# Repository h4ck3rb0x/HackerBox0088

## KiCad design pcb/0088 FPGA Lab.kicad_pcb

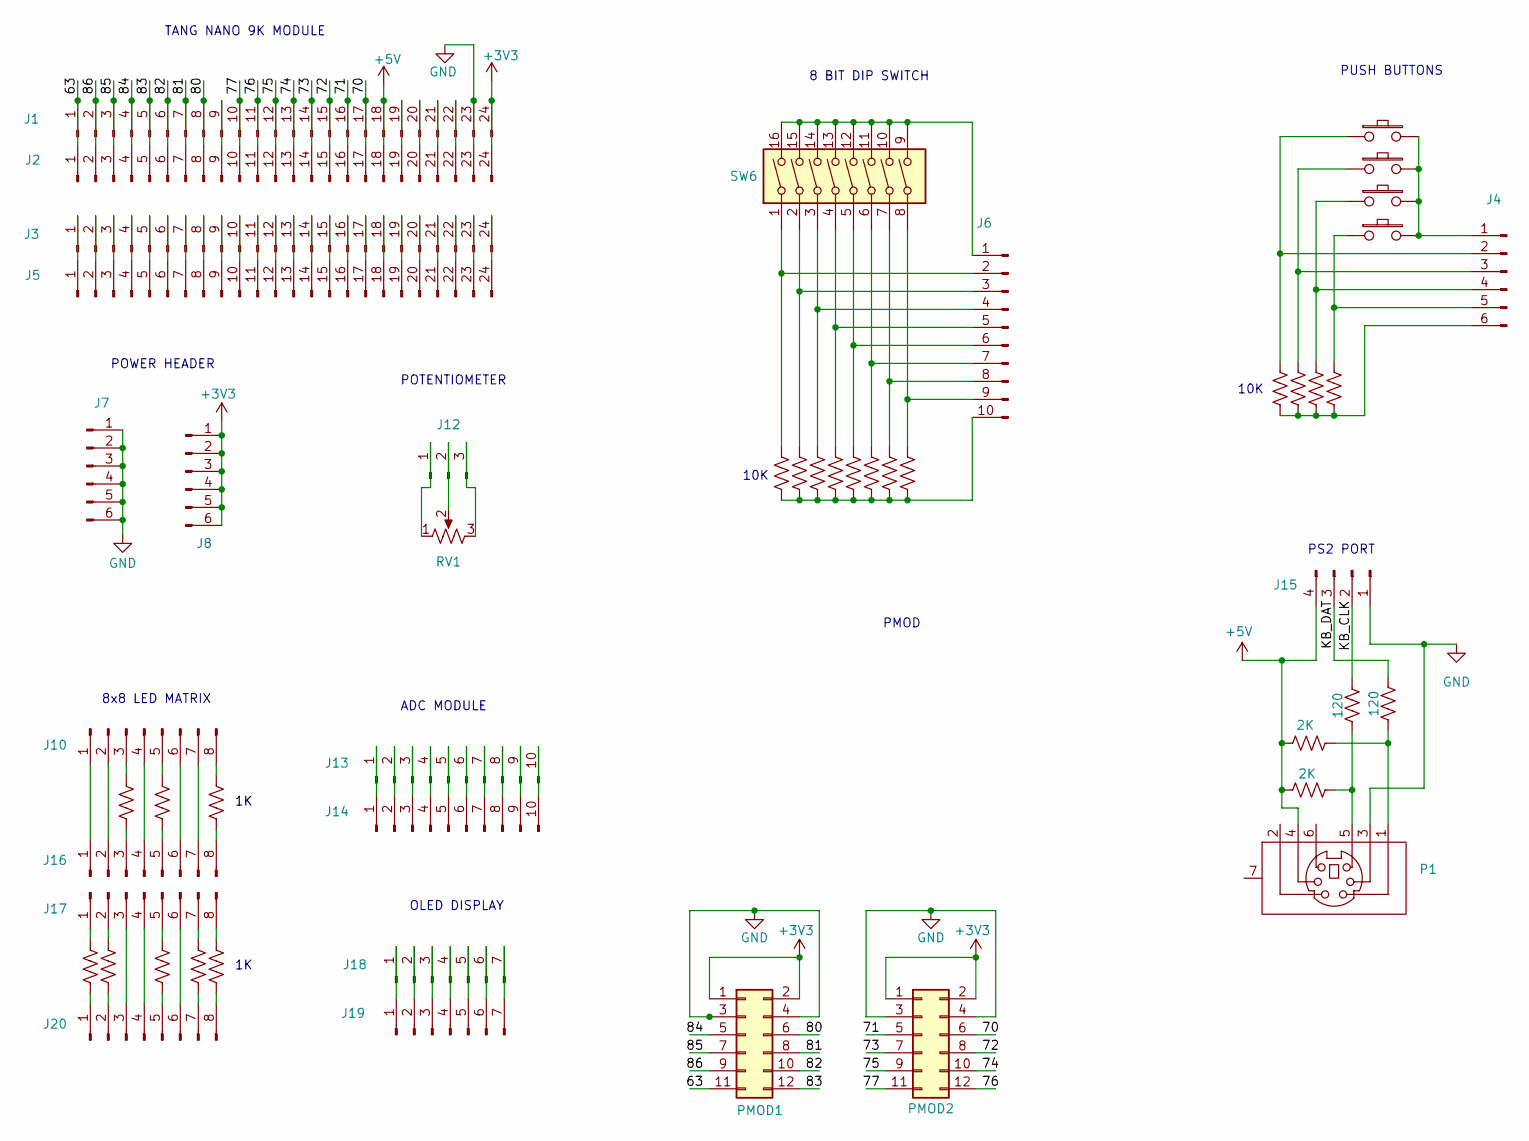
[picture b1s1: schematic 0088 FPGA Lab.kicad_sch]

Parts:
J1, J2, J3, J5: Conn_01x24_Male; PinHeader_1x24_P2.54mm_Vertical
J4, J7, J8: Conn_01x06_Male; PinHeader_1x06_P2.54mm_Vertical
J6, J13, J14: Conn_01x10_Male; PinHeader_1x10_P2.54mm_Vertical
J10, J16, J17, J20: Conn_01x08_Male; PinHeader_1x08_P2.54mm_Vertical
J12: Conn_01x03_Male; PinHeader_1x03_P2.54mm_Vertical
J15: Conn_01x04_Male; PinHeader_1x04_P2.54mm_Vertical
J18, J19: Conn_01x07_Male; PinHeader_1x07_P2.54mm_Vertical
P1: Connector_Mini-DIN_Female_6Pin_2rows
PMOD1, PMOD2: Conn_02x06_Odd_Even; PinSocket_2x06_P2.54mm_Horizontal
R1, R2, R4, R5, R6, R7, R8, R9, R10, R11, R12: 10K; R_1206_3216Metric_Pad1.30x1.75mm_HandSolder
R3: 10k; R_1206_3216Metric_Pad1.30x1.75mm_HandSolder
R13, R14: 2K; R_1206_3216Metric_Pad1.30x1.75mm_HandSolder
R15, R16: 120; R_1206_3216Metric_Pad1.30x1.75mm_HandSolder
R17, R18, R19, R20, R21, R22, R23, R24: 1K; R_1206_3216Metric_Pad1.30x1.75mm_HandSolder
RV1: R_Potentiometer_US; Potentiometer_Bourns_PTV09A-1_Single_Vertical
SW1, SW2, SW3, SW4: SW_PUSH_BUTTON; SW_TH_Tactile_Omron_B3F-10xx
SW6: SW_DIP_x08; SW_DIP_SPSTx08_Slide_9.78x22.5mm_W7.62mm_P2.54mm

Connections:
+5V: J1.18, J2.18, J15.4, P1.4, R13.2, R14.2
/63: J1.1, J2.1, PMOD1.11
/70: J1.17, J2.17, PMOD2.6
/71: J1.16, J2.16, PMOD2.5
/72: J1.15, J2.15, PMOD2.8
/73: J1.14, J2.14, PMOD2.7
/74: J1.13, J2.13, PMOD2.10
/75: J1.12, J2.12, PMOD2.9
/76: J1.11, J2.11, PMOD2.12
/77: J1.10, J2.10, PMOD2.11
/80: J1.8, J2.8, PMOD1.6
/81: J1.7, J2.7, PMOD1.8
/82: J1.6, J2.6, PMOD1.10
/83: J1.5, J2.5, PMOD1.12
/84: J1.4, J2.4, PMOD1.5
/85: J1.3, J2.3, PMOD1.7
/86: J1.2, J2.2, PMOD1.9
/KB_CLK: J15.2, R15.1
/KB_DAT: J15.3, R16.1
unnamed: J1.9, J2.9
unnamed: J1.19, J2.19
unnamed: J1.20, J2.20
unnamed: J1.21, J2.21
unnamed: J1.22, J2.22
unnamed: J3.1, J5.1
unnamed: J3.2, J5.2
unnamed: J3.3, J5.3
unnamed: J3.4, J5.4
unnamed: J3.5, J5.5
unnamed: J3.6, J5.6
unnamed: J3.7, J5.7
unnamed: J3.8, J5.8
unnamed: J3.9, J5.9
unnamed: J3.10, J5.10
unnamed: J3.11, J5.11
unnamed: J3.12, J5.12
unnamed: J3.13, J5.13
unnamed: J3.14, J5.14
unnamed: J3.15, J5.15
unnamed: J3.16, J5.16
unnamed: J3.17, J5.17
unnamed: J3.18, J5.18
unnamed: J3.19, J5.19
unnamed: J3.20, J5.20
unnamed: J3.21, J5.21
unnamed: J3.22, J5.22
unnamed: J3.23, J5.23
unnamed: J3.24, J5.24
unnamed: J4.1, SW1.2, SW2.2, SW3.2, SW4.2
unnamed: J4.2, R1.2, SW1.1
unnamed: J4.3, R2.2, SW2.1
unnamed: J4.4, R3.2, SW3.1
unnamed: J4.5, R4.2, SW4.1
unnamed: J4.6, R1.1, R2.1, R3.1, R4.1
unnamed: J6.1, SW6.9, SW6.10, SW6.11, SW6.12, SW6.13, SW6.14, SW6.15, SW6.16
unnamed: J6.2, R5.2, SW6.1
unnamed: J6.3, R6.2, SW6.2
unnamed: J6.4, R7.2, SW6.3
unnamed: J6.5, R8.2, SW6.4
unnamed: J6.6, R9.2, SW6.5
unnamed: J6.7, R10.2, SW6.6
unnamed: J6.8, R11.2, SW6.7
unnamed: J6.9, R12.2, SW6.8
unnamed: J6.10, R5.1, R6.1, R7.1, R8.1, R9.1, R10.1, R11.1, R12.1
unnamed: J10.1, J16.1
unnamed: J10.2, J16.2
unnamed: J10.3, R17.2
unnamed: J10.4, J16.4
unnamed: J10.5, R18.2
unnamed: J10.6, J16.6
unnamed: J10.7, J16.7
unnamed: J10.8, R19.2
unnamed: J12.1, RV1.1
unnamed: J12.2, RV1.2
unnamed: J12.3, RV1.3
unnamed: J13.1, J14.1
unnamed: J13.2, J14.2
unnamed: J13.3, J14.3
unnamed: J13.4, J14.4
unnamed: J13.5, J14.5
unnamed: J13.6, J14.6
unnamed: J13.7, J14.7
unnamed: J13.8, J14.8
unnamed: J13.9, J14.9
unnamed: J13.10, J14.10
unnamed: J16.3, R17.1
unnamed: J16.5, R18.1
unnamed: J16.8, R19.1
unnamed: J17.1, R20.2
unnamed: J17.2, R21.2
unnamed: J17.3, J20.3
unnamed: J17.4, J20.4
unnamed: J17.5, R22.2
unnamed: J17.6, J20.6
unnamed: J17.7, R23.2
unnamed: J17.8, R24.2
unnamed: J18.1, J19.1
unnamed: J18.2, J19.2
unnamed: J18.3, J19.3
unnamed: J18.4, J19.4
unnamed: J18.5, J19.5
unnamed: J18.6, J19.6
unnamed: J18.7, J19.7
unnamed: J20.1, R20.1
unnamed: J20.2, R21.1
unnamed: J20.5, R22.1
unnamed: J20.7, R23.1
unnamed: J20.8, R24.1
unnamed: P1.1, R13.1, R16.2
unnamed: P1.5, R14.1, R15.2

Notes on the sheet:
10K
8x8 LED MATRIX
ADC MODULE
TANG NANO 9K MODULE
PUSH BUTTONS
8 BIT DIP SWITCH
PS2 PORT
PMOD
POTENTIOMETER
POWER HEADER
OLED DISPLAY

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
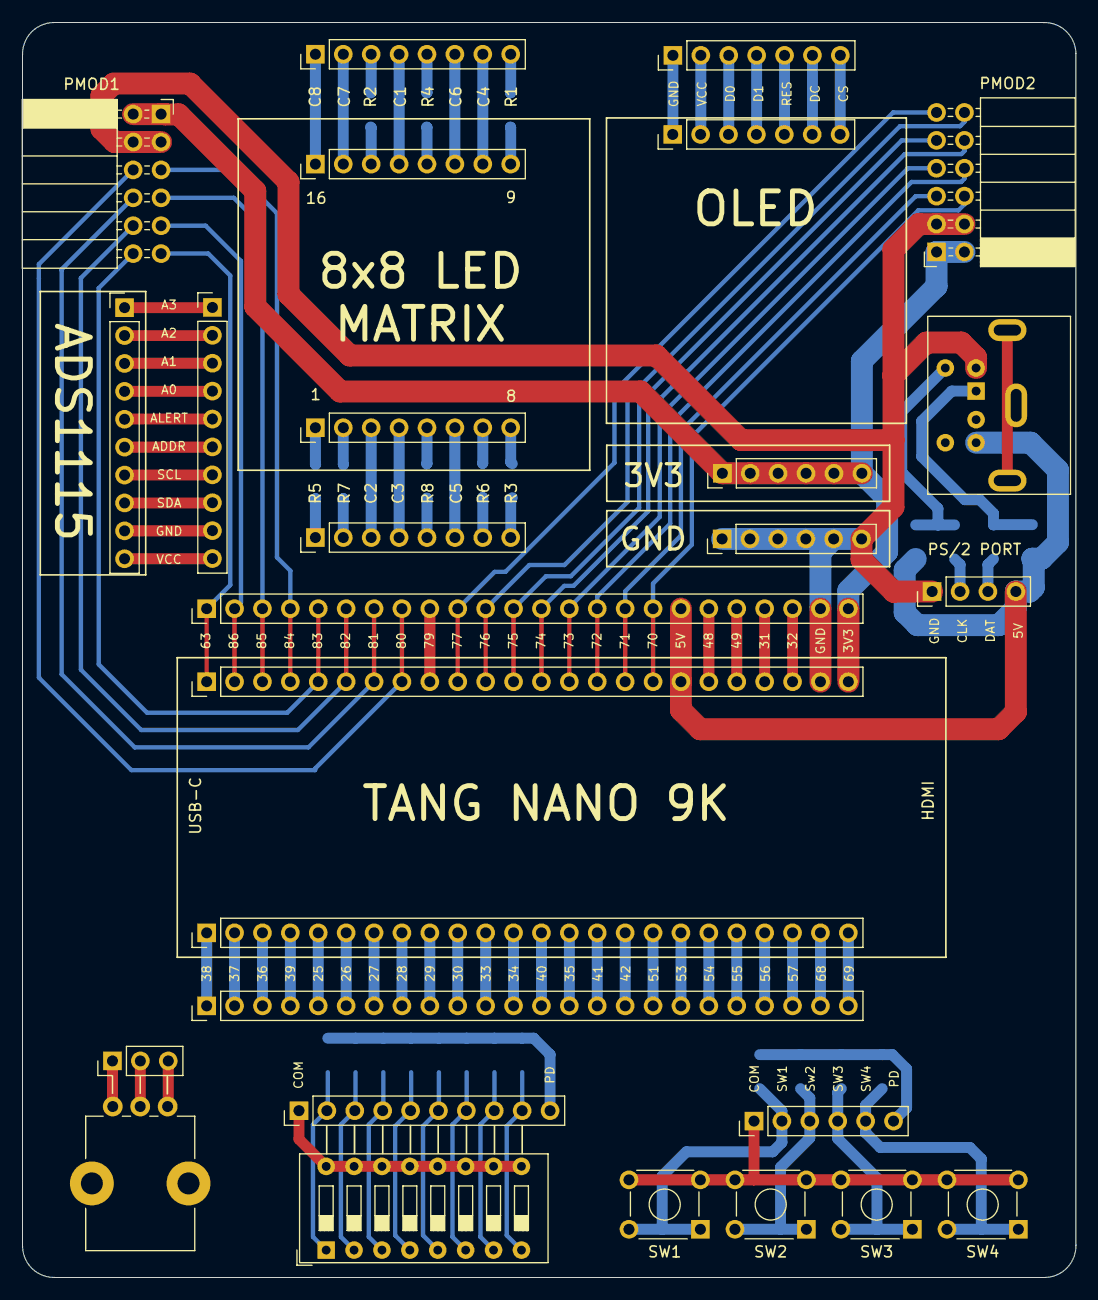
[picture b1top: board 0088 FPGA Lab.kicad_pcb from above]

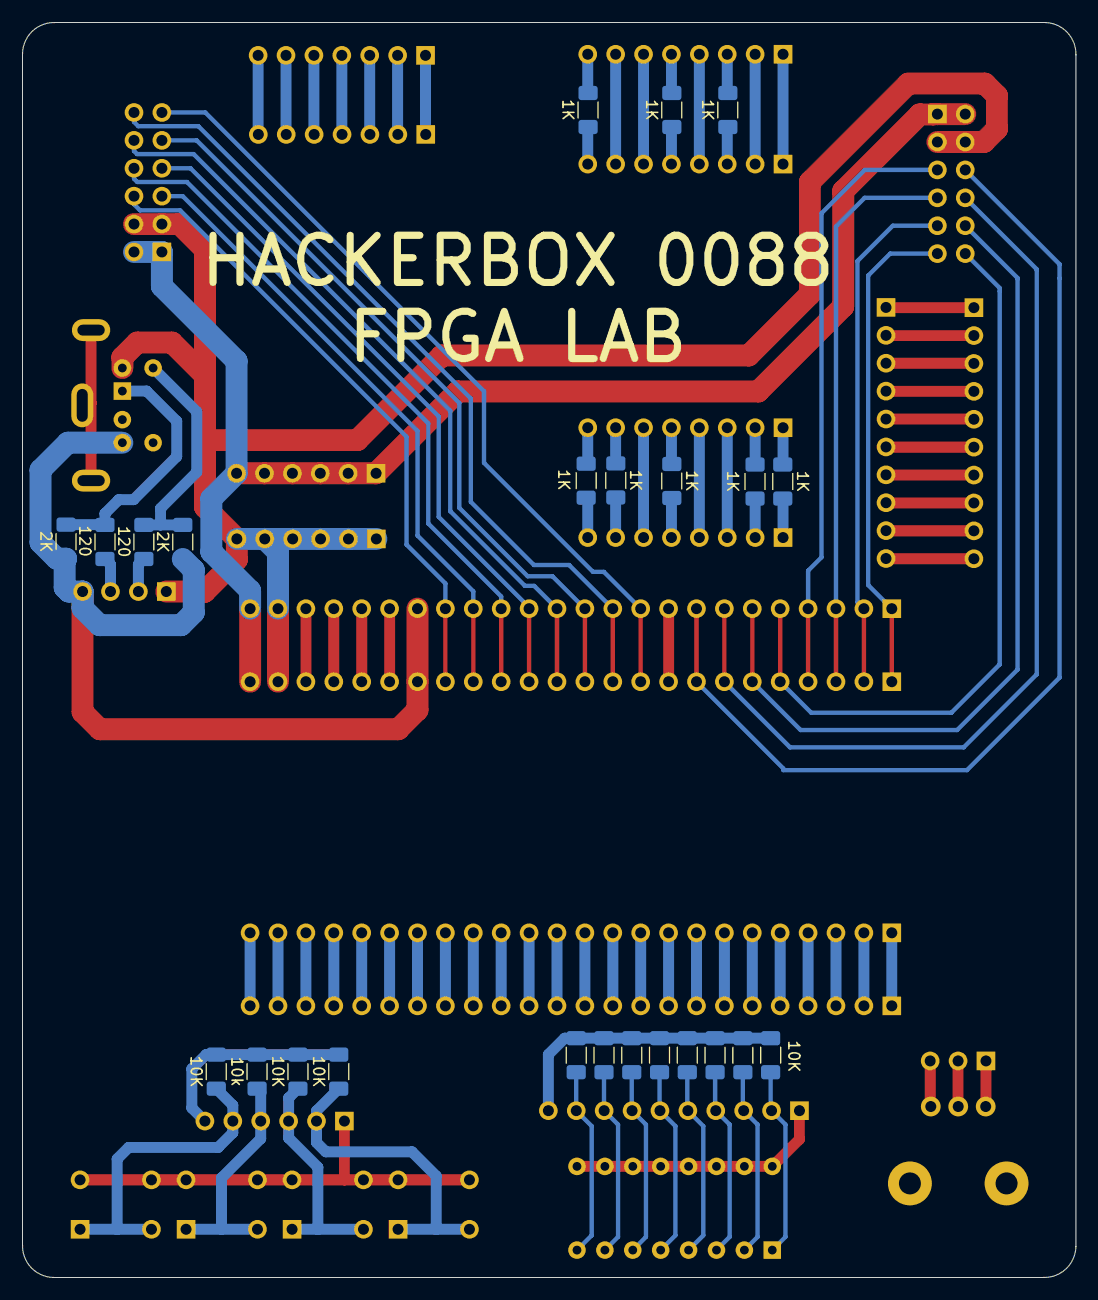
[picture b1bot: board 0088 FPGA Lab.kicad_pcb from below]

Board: 2 copper layers, 95.9 x 114.3 mm, 51 parts (24 on the bottom side), 112 nets.

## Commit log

2023-02-22 Create void
